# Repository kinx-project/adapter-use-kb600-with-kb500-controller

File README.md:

Are you using an older Kinesis Advantage ergonomic keyboard [with a custom
keyboard
controller](https://michael.stapelberg.ch/posts/2020-07-09-kint-kinesis-keyboard-controller/)?

This adapter boards **allows you to keep using your old custom keyboard
controller in a new Kinesis Advantage 2 keyboard**!

This adapter was split out of the [kinT keyboard
controller](https://github.com/kinx-project/kint) project, which is a
replacement controller for your Kinesis Advantage or Advantage 2 ergonomic
keyboards.

## Quick overview

<table border="0" width="100%">
<tr>
<td width="33%">

3D render (front)
</td>
<td width="33%">

3D render (back)
</td>
<td width="33%">

schematic
</td>
</tr>
</table>

## Building your own adapter board

1. Follow [“Buying the board and components (Bill of
   materials)”](https://github.com/kinx-project/adapter-use-kb600-with-kb500-controller#buying-the-board-and-components-bill-of-materials). When
   ordering from OSH Park (board) and Digi-Key (components), you’ll get the
   minimum quantity of 3 boards for 5.15 USD (1.71 USD per board), and one set
   of components for 3.69 USD.

1. Wait for the components to arrive. When ordering from big shops like Digi-Key
   or Mouser, this typically takes 2 days to many places in the world.

1. Wait for the boards to arrive. This takes 6 days in the best case when
   ordering from OSH Park with their Super Swift Service option. In general, the
   longer you are willing to wait, the cheaper it is going to get.

1. Follow [the soldering
   guide](https://github.com/kinx-project/adapter-use-kb600-with-kb500-controller#soldering). This
   will take about 10 minutes.

## Buying the board and components (Bill of materials)

To buy the board, you can [order the u6w5 adapter board from OSH
Park](https://oshpark.com/shared_projects/gv2aPVJn), or upload the
[adapter-u6w5.kicad_pcb
file](https://github.com/kinx-project/adapter-use-kb600-with-kb500-controller/blob/master/kicad/adapter-u6w5.kicad_pcb)
to the manufacturing service you prefer.

To buy the components, check out the [u6w5 adapter BOM in the Octopart BOM
tool](https://octopart.com/bom-tool/x01g9U4U), from where you can conveniently
buy all components via Digi-Key or Mouser.

For your convenience, this is the full BOM (links go to Octopart):

| Part Number                                                                 | Count | Cost  | Description               |
|-----------------------------------------------------------------------------|-------|-------|---------------------------|
| [Molex 39-53-2135](https://octopart.com/39-53-2135-molex-7670149?r=sp)      | 2     | $1.06 | 13 position FPC connector |
| [Preci-Dip 801-87-010-10-001101](https://octopart.com/801-87-010-10-001101) | 2     | $0.78 |                           |
|                                                                             |       | $3.69 |                           |

Note: any female pin header that you still may have lying around should work
fine.

## Soldering

If you prefer visual instructions, check out the soldering instructions video on
YouTube:

All the soldering connections on the u6w5 adapter board are easy to make, so the
whole assembly can be done at home, with a cheap soldering iron and basic
electronic hobby equipment.

For example, I used the [Miniware TS100 soldering
iron](https://hackaday.com/2017/07/24/review-ts100-soldering-iron/), which can
be found for 50-60 EUR or USD.

A build takes about 10 minutes of time and involves making 46 soldering
connections.

If you’re new to soldering, check out [this excellent soldering reference card
from adafruit](https://twitter.com/zekjur/status/952596267884056576).

### Soldering instructions

1. Populate the FPC connector.

1. Populate the female pin header.

1. Repeat for the second board.

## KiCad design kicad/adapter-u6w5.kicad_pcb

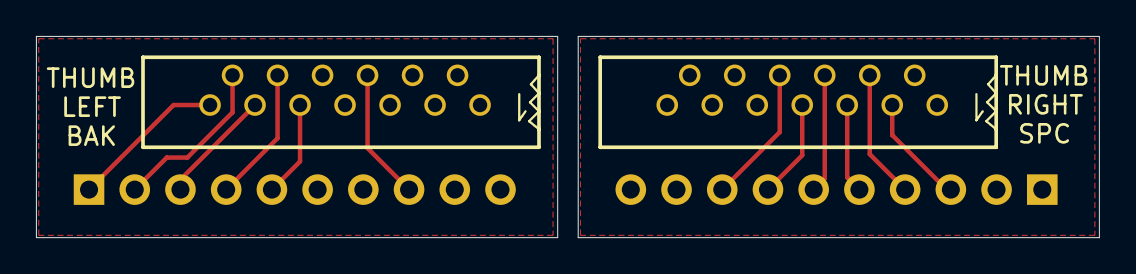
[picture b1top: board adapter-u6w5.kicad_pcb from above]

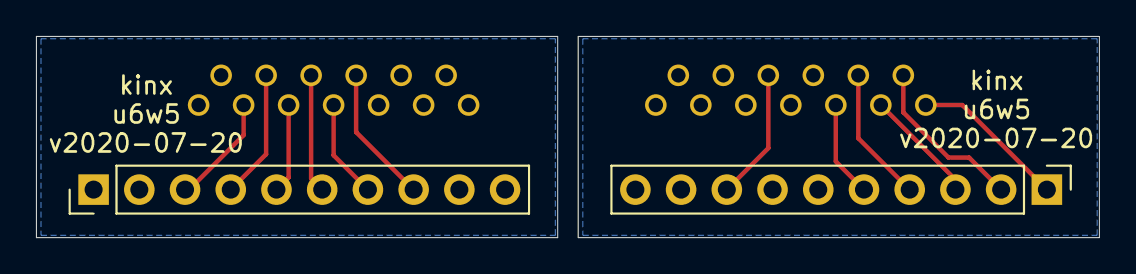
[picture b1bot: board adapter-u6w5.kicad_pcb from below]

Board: 2 copper layers, 59.1 x 11.2 mm, 4 parts (2 on the bottom side), 12 nets.

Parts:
J1: THUMB_RIGHT_SPC_KB600; 39-53-2135
J5: THUMB LEFT BAK; PinHeader_1x10_P2.54mm_Vertical
J6: THUMB RIGHT SPC; PinHeader_1x10_P2.54mm_Vertical
J8: THUMB_LEFT_BAK_KB600; 39-53-2135

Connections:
/COL_5_L: J5.5, J8.9
/COL_5_R: J1.8, J6.8
/COL_6_L: J5.4, J8.10
/COL_6_R: J1.7, J6.7
/ROW_2_L: J5.2, J8.12
/ROW_3_L: J5.8, J8.6
/ROW_4_L: J5.1, J8.13
/ROW_5_L: J5.3, J8.11
/ROW_6_R: J1.3, J6.3
/ROW_7_R: J1.4, J6.4
/ROW_8_R: J1.5, J6.5
/ROW_9_R: J1.6, J6.6

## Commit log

2020-06-29 fork u6w5 adapter from kinT controller
2020-06-29 adjust board size
2020-06-30 panelization: add mouse bites/tab and cut lines
2020-06-30 route
2020-07-02 cut boards apart as per oshpark support
    The fab will add the required tabs.
2020-07-20 move parts around, rotate correctly, re-route
2020-07-28 update artifacts for verified-working v2020-07-20

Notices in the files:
README.md:
License: CC BY-SA 4.0
